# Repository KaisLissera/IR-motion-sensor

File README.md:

# IR-motion-sensor
*University graduation work*  

Система электронного хронометража для конных соревнований, временные засечки определяются по моменту пересечения луча

## TODO:
### HW
- Заменить SX1276 на аналогичный модуль без интегрированной антенны или RFM95W
- Добавить на плате земляной полигон без маски для тестирования
- ZQ3 - дорожки от кварца должны быть на верхней части платы
- Заменить все резисторы и конденсаторы 0402 на 0603
- Заменить индуктивности в фильтре аналогового питания на дроссели BLM18AG102 0603
### 3d Model
- Переделать отверстие под USB порт
- ~~Подобрать размер кнопки на передней панели~~
- Облегчить корпус

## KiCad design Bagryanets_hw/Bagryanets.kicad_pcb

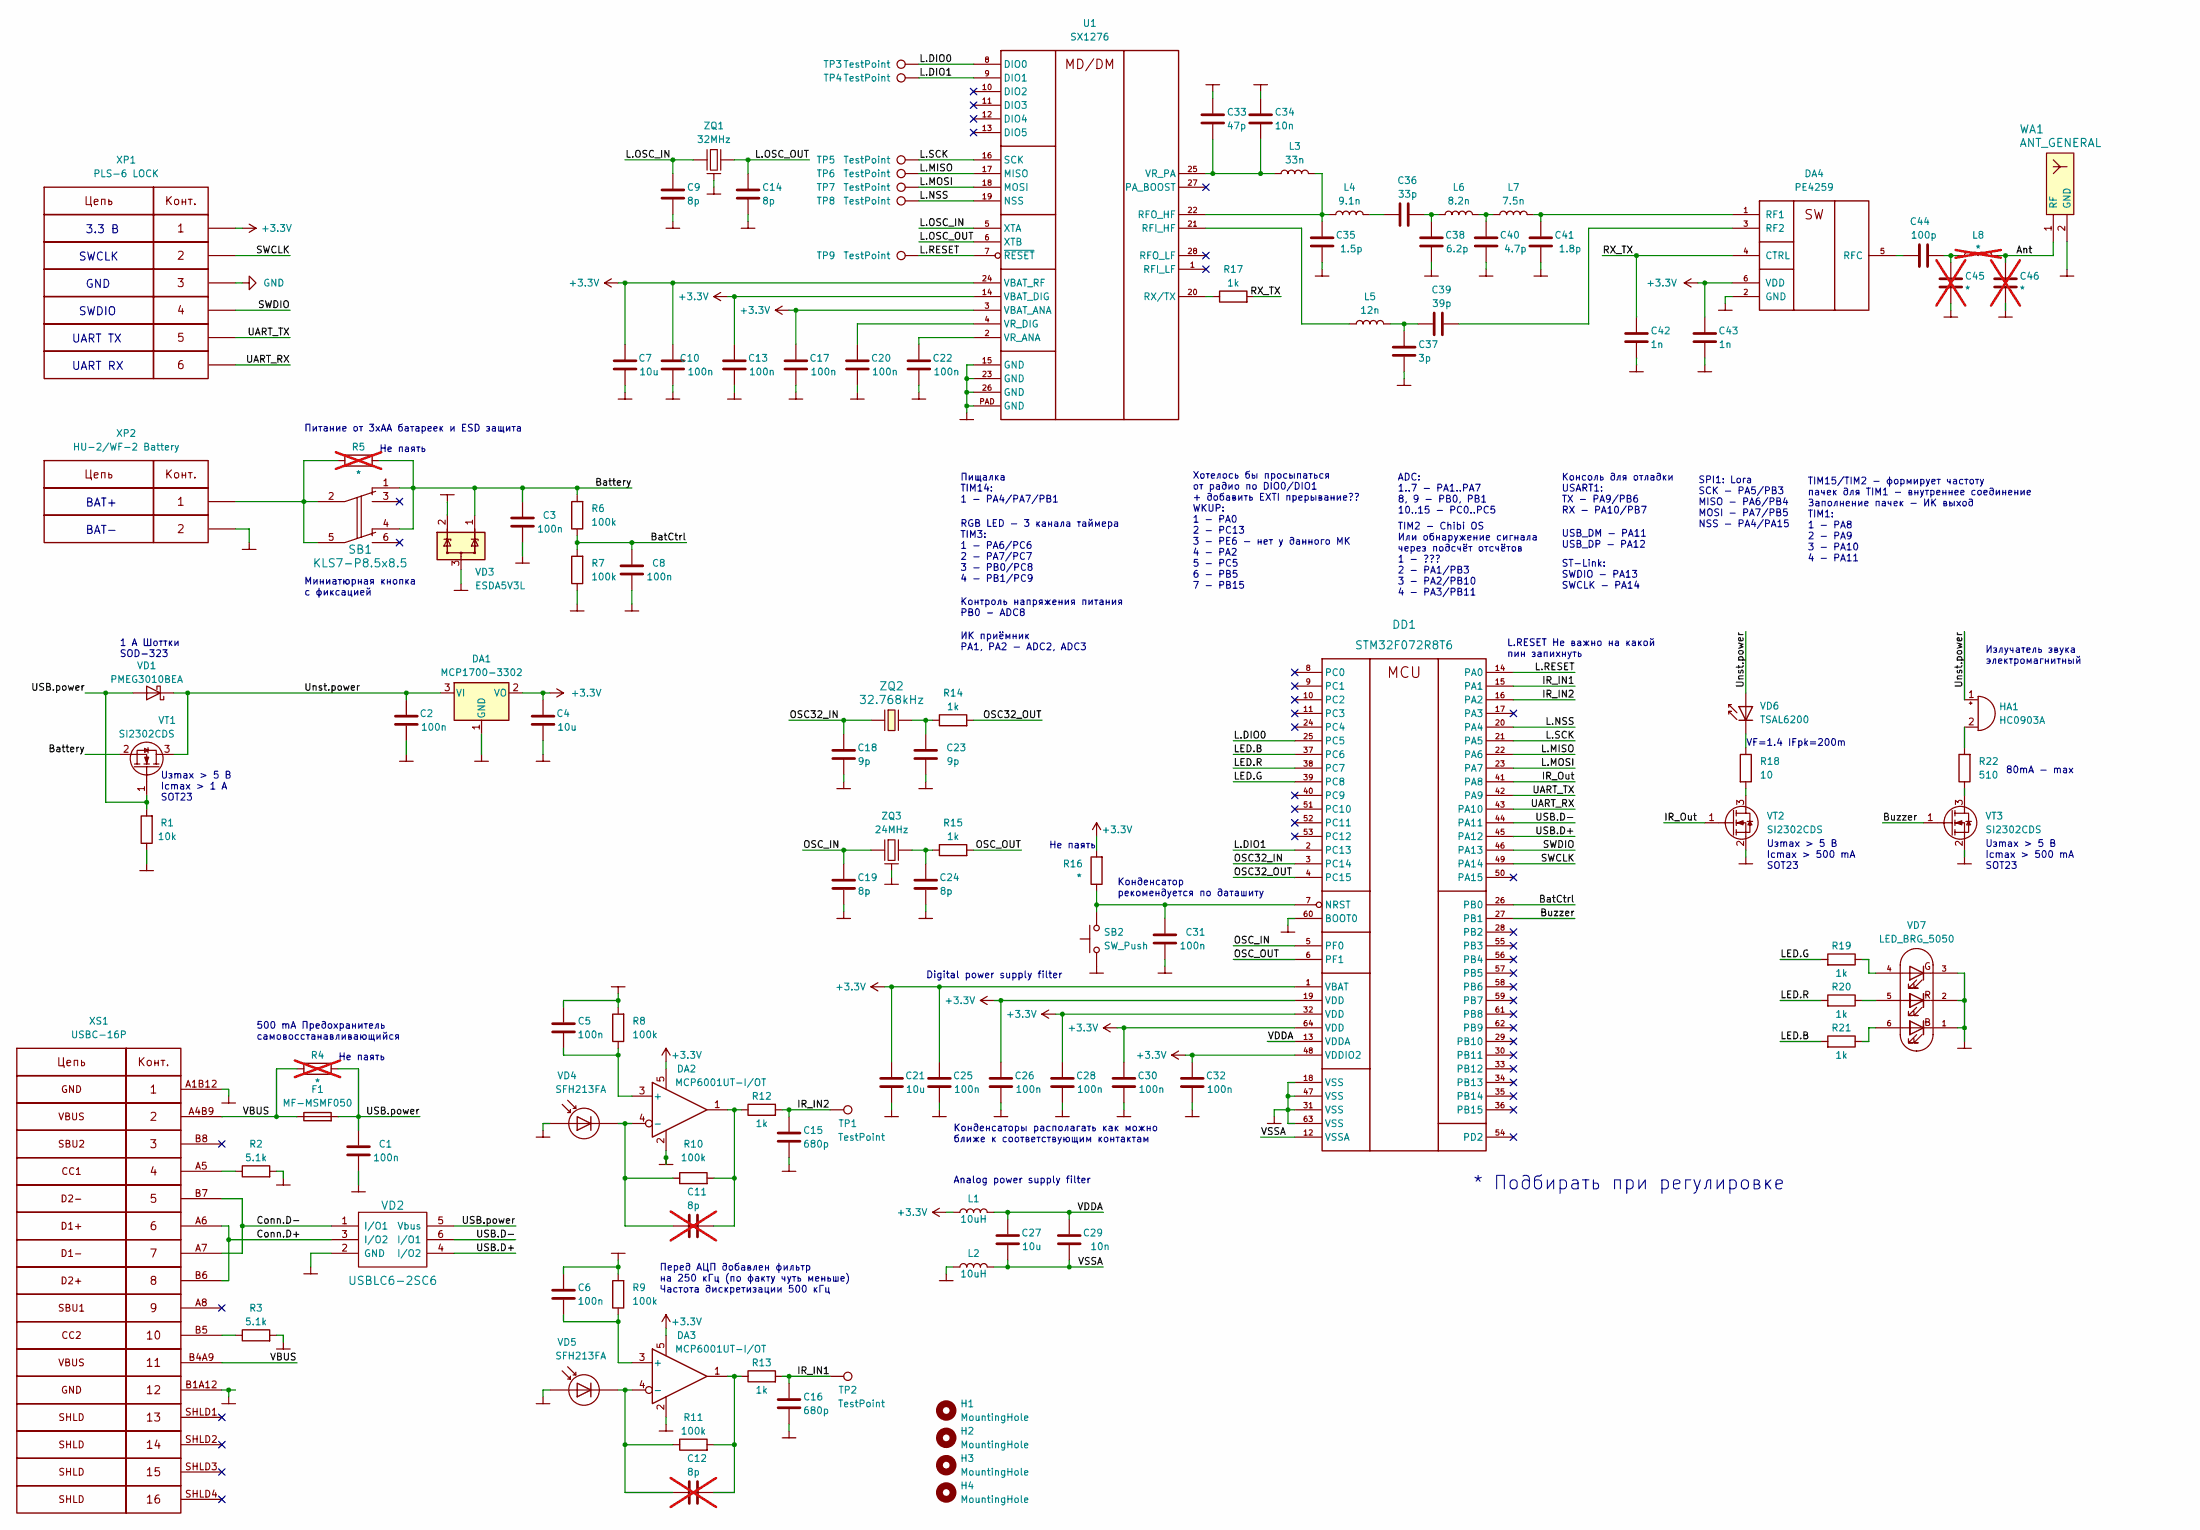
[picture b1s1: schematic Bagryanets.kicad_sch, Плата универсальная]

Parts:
C1, C2, C3, C5, C6, C8, C10, C13, C17, C20, C22, C25, C26, C28, C30, C31, C32: 100n; CAP_0402
C4, C7, C21, C27: 10u; CAP_0603
C9, C14, C19, C24: 8p; CAP_0402
C11, C12: 8p; CAP_0402; not fitted
C15, C16: 680p; CAP_0402
C18, C23: 9p; CAP_0402
C29, C34: 10n; CAP_0402
C33: 47p; CAP_0402
C35: 1.5p; CAP_0402
C36: 33p; CAP_0402
C37: 3p; CAP_0402
C38: 6.2p; CAP_0402
C39: 39p; CAP_0402
C40: 4.7p; CAP_0402
C41: 1.8p; CAP_0402
C42, C43: 1n; CAP_0402
C44: 100p; CAP_0402
C45, C46: *; CAP_0402; not fitted
DA1: MCP1700-3302; SOT23-3
DA2, DA3: MCP6001UT-I/OT; SOT23-5
DA4: PE4259; SC70
DD1: STM32F072R8T6; LQFP64
F1: MF-MSMF050; Fuse_1812_4532Metric_Pad1.30x3.40mm_HandSolder
H1, H2, H3, H4: MountingHole; MountingHole_2.5mm
HA1: HC0903A; MagneticBuzzer_CUI_CST-931RP-A
L1, L2: 10uH; IND_0805
L3: 33n; IND_0402
L4: 9.1n; IND_0402
L5: 12n; IND_0402
L6: 8.2n; IND_0402
L7: 7.5n; IND_0402
L8: *; IND_0402; not fitted
R1: 10k; RES_0603
R2, R3: 5.1k; RES_0603
R4, R5: *; RES_0402; not fitted
R6, R7, R8, R9, R10, R11: 100k; RES_0603
R12, R13, R14, R15, R19, R20, R21: 1k; RES_0603
R16: *; RES_0603
R17: 1k; RES_0402
R18: 10; RES_0402
R22: 510; RES_0402
SB1: KLS7-P8.5x8.5
SB2: SW_Push; SW_PUSH_6mm
TP1, TP2, TP3, TP4, TP5, TP6, TP7, TP8, TP9: TestPoint; TESTPOINT_1MM
U1: SX1276; QFN-28_EP_6x6_Pitch0.65mm
VD1: PMEG3010BEA; SOD323
VD2: USBLC6-2SC6; SOT23-6
VD3: ESDA5V3L; SOT-23
VD4, VD5: SFH213FA; LED_D5.0mm
VD6: TSAL6200; LED_D5.0mm_Clear
VD7: LED_BRG_5050; LED_RGB_5050-6
VT1, VT2, VT3: SI2302CDS; SOT23-3
WA1: ANT_GENERAL; Antenna_868_Bagryanets
XP1: PLS-6 LOCK; PinHeader_1x06_P2.54mm_Horizontal
XP2: HU-2/WF-2 Battery; PinHeader_1x02_P2.54mm_Horizontal
XS1: USBC-16P; USBC_10PF-074
ZQ1: 32MHz; 03225C4
ZQ2: 32.768kHz; Crystal_SMD_3215-2Pin_3.2x1.5mm
ZQ3: 24MHz; 03225C4

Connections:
+3V3: C4.2, C7.2, C10.2, C13.2, C17.2, C21.2, C25.2, C26.2, C28.2, C30.2, C32.2, C43.1, DA1.2 (VO), DA2.5, DA3.5, DA4.6 (VDD), DD1.1 (VBAT), DD1.19 (VDD), DD1.32 (VDD), DD1.48 (VDDIO2), DD1.64 (VDD), L1.1, R16.2, U1.3 (VBAT_ANA), U1.14 (VBAT_DIG), U1.24 (VBAT_RF), XP1.1
/Ant: C46.1, L8.2, WA1.1 (RF)
/BatCtrl: C8.2, DD1.26 (PB0), R6.1, R7.2
/Battery: C3.2, R5.2, R6.2, SB1.1, SB1.4, VD3.1 (IO1), VT1.2 (S)
/Buzzer: DD1.27 (PB1), VT3.1 (G)
/Conn.D+: VD2.3 (I/O2), XS1.A6 (DP1), XS1.B6 (DP2)
/Conn.D-: VD2.1 (I/O1), XS1.A7 (DN1), XS1.B7 (DN2)
/IR_IN1: C16.1, DD1.15 (PA1), R13.2, TP2.1
/IR_IN2: C15.1, DD1.16 (PA2), R12.2, TP1.1
/IR_Out: DD1.41 (PA8), VT2.1 (G)
/L.DIO0: DD1.25 (PC5), TP3.1, U1.8 (DIO0)
/L.DIO1: DD1.2 (PC13), TP4.1, U1.9 (DIO1)
/L.MISO: DD1.22 (PA6), TP6.1, U1.17 (MISO)
/L.MOSI: DD1.23 (PA7), TP7.1, U1.18 (MOSI)
/L.NSS: DD1.20 (PA4), TP8.1, U1.19 (NSS)
/L.OSC_IN: C9.1, U1.5 (XTA), ZQ1.1
/L.OSC_OUT: C14.1, U1.6 (XTB), ZQ1.2
/L.RESET: DD1.14 (PA0), TP9.1, U1.7 (~RESET)
/L.SCK: DD1.21 (PA5), TP5.1, U1.16 (SCK)
/LED.B: DD1.37 (PC6), R21.2
/LED.G: DD1.39 (PC8), R19.2
/LED.R: DD1.38 (PC7), R20.2
/OSC32_IN: C18.2, DD1.3 (PC14), ZQ2.1
/OSC32_OUT: DD1.4 (PC15), R14.2
/OSC_IN: C19.2, DD1.5 (PF0), ZQ3.1
/OSC_OUT: DD1.6 (PF1), R15.2
/RX_TX: C42.1, DA4.4 (CTRL), R17.2
/SWCLK: DD1.49 (PA14), XP1.2
/SWDIO: DD1.46 (PA13), XP1.4
/UART_RX: DD1.43 (PA10), XP1.6
/UART_TX: DD1.42 (PA9), XP1.5
/USB.D+: DD1.45 (PA12), VD2.4 (I/O2)
/USB.D-: DD1.44 (PA11), VD2.6 (I/O1)
/USB.power: C1.2, F1.2, R1.2, R4.2, VD1.A, VD2.5 (Vbus), VT1.1 (G)
/Unst.power: C2.2, DA1.3 (VI), HA1.1 (-), VD1.C, VD6.2 (A), VT1.3 (D)
/VBUS: F1.1, R4.1, XS1.A4B9 (VBUS), XS1.B4A9 (VBUS)
/VDDA: C27.2, C29.2, DD1.13 (VDDA), L1.2
/VSSA: C27.1, C29.1, DD1.12 (VSSA), L2.2
unnamed: C11.1, DA2.1, R10.2, R12.1
unnamed: C12.1, DA3.1, R11.2, R13.1
unnamed: C23.2, R14.1, ZQ2.2
unnamed: C24.2, R15.1, ZQ3.2
unnamed: C36.1, L4.2
unnamed: C36.2, C38.2, L6.1
unnamed: C37.1, C39.1, L5.2
unnamed: C40.2, L6.2, L7.1
unnamed: C44.2, C45.1, L8.1
unnamed: C5.2, DA2.3 (+), R8.1
unnamed: C11.2, DA2.4 (-), R10.1, VD4.1 (K)
unnamed: C6.2, DA3.3 (+), R9.1
unnamed: C12.2, DA3.4 (-), R11.1, VD5.1 (K)
unnamed: C41.2, DA4.1 (RF1), L7.2
unnamed: C39.2, DA4.3 (RF2)
unnamed: C44.1, DA4.5 (RFC)
unnamed: C31.2, DD1.7 (NRST), R16.1, SB2.2
unnamed: HA1.2 (+), R22.2
unnamed: R5.1, SB1.2, SB1.5, XP2.1
unnamed: L5.1, U1.21 (RFI_HF)
unnamed: C35.2, L3.2, L4.1, U1.22 (RFO_HF)
unnamed: R17.1, U1.20 (RX/TX)
unnamed: C22.2, U1.2 (VR_ANA)
unnamed: C20.2, U1.4 (VR_DIG)
unnamed: C33.2, C34.2, L3.1, U1.25 (VR_PA)
unnamed: R18.1, VD6.1 (K)
unnamed: R19.1, VD7.4 (BA)
unnamed: R20.1, VD7.5 (GA)
unnamed: R21.1, VD7.6 (RA)
unnamed: R18.2, VT2.3 (D)
unnamed: R22.1, VT3.3 (D)
unnamed: R2.1, XS1.A5 (CC1)
unnamed: R3.1, XS1.B5 (CC2)

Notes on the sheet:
GND
80mA - max
Перед АЦП добавлен фильтр на 250 кГц (по факту чуть меньше) Частота дискретизации 500 кГц
Uзmax > 5 В Iсmax > 500 mА SOT23
SWDIO
Контроль напряжения питания PB0 - ADC8
500 mA Предохранитель самовосстанавливающийся
TIM15/TIM2 - формирует частоту пачек для TIM1 - внутреннее соединение Заполнение пачек - ИК выход TIM1: 1 - PA8 2 - PA9 3 - PA10 4 - PA11
Не паять
Uзmax > 5 В Iсmax > 1 А SOT23
L.RESET Не важно на какой пин запихнуть
ИК приёмник PA1, PA2 - ADC2, ADC3
Излучатель звука электромагнитный
TIM2 - Chibi OS Или обнаружение сигнала через подсчёт отсчётов 1 - ??? 2 - PA1/PB3 3 - PA2/PB10 4 - PA3/PB11
BAT-
Analog power supply filter
RGB LED - 3 канала таймера TIM3: 1 - PA6/PC6 2 - PA7/PC7 3 - PB0/PC8 4 - PB1/PC9
3.3 В
UART TX
USB_DM - PA11 USB_DP - PA12
* Подбирать при регулировке
BAT+
Миниатюрная кнопка с фиксацией
Консоль для отладки USART1: TX - PA9/PB6 RX - PA10/PB7
Хотелось бы просыпаться от радио по DIO0/DIO1 + добавить EXTI прерывание?? WKUP: 1 - PA0 2 - PC13 3 - PE6 - нет у данного МК 4 - PA2 5 - PC5 6 - PB5 7 - PB15
Пищалка TIM14: 1 - PA4/PA7/PB1
Digital power supply filter
Питание от 3хАА батареек и ESD защита
Конденсатор рекомендуется по даташиту
VF=1.4 IFpk=200m
ADC: 1..7 - PA1..PA7 8, 9 - PB0, PB1 10..15 - PC0..PC5
ST-Link: SWDIO - PA13 SWCLK - PA14
1 А Шоттки SOD-323
SWCLK
UART RX
Конденсаторы располагать как можно ближе к соответствующим контактам
SPI1: Lora SCK - PA5/PB3 MISO - PA6/PB4 MOSI - PA7/PB5 NSS - PA4/PA15

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
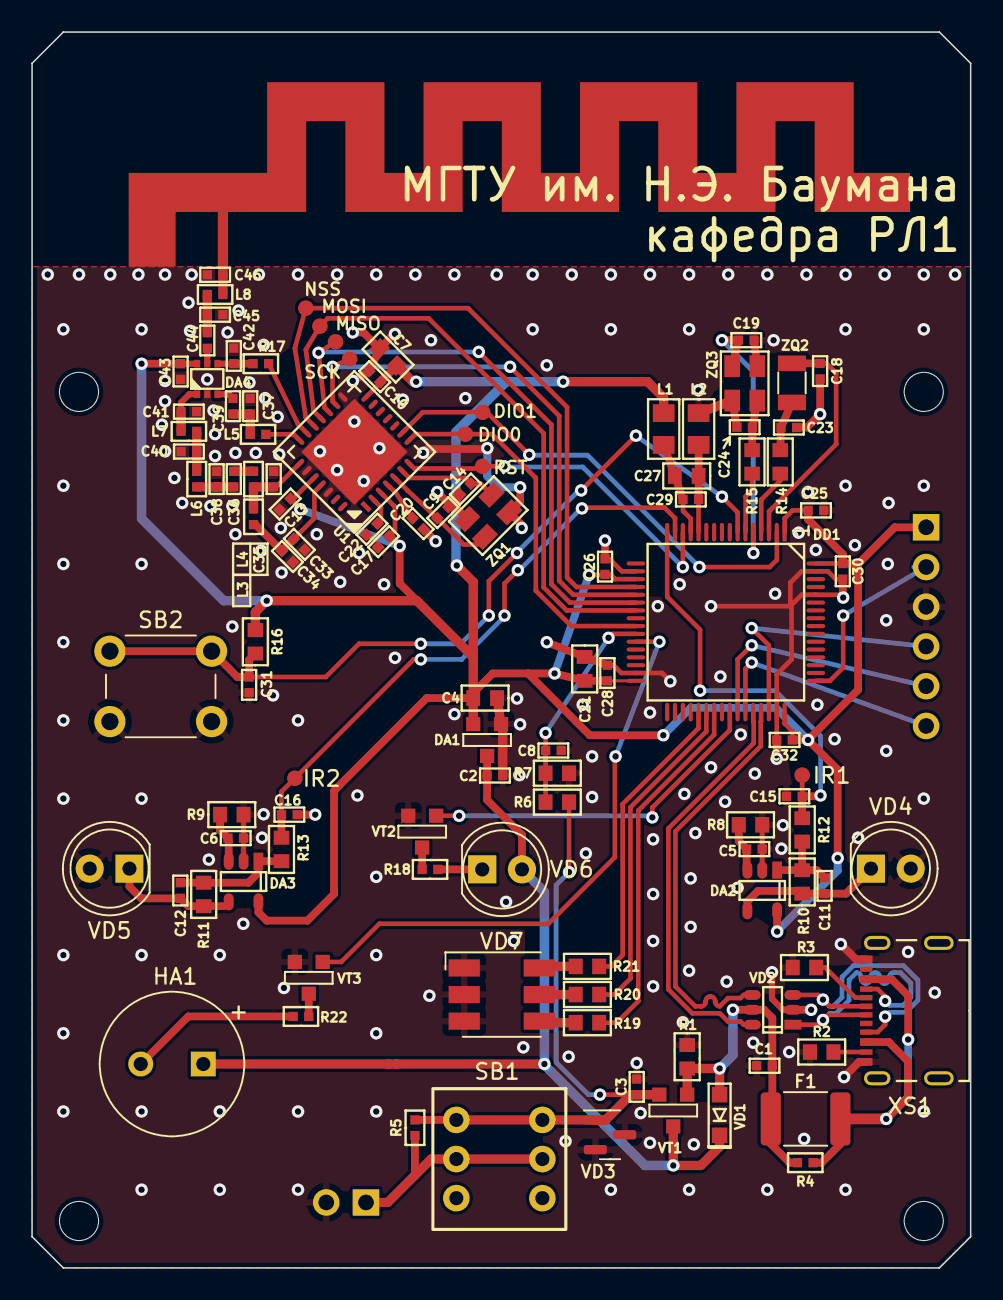
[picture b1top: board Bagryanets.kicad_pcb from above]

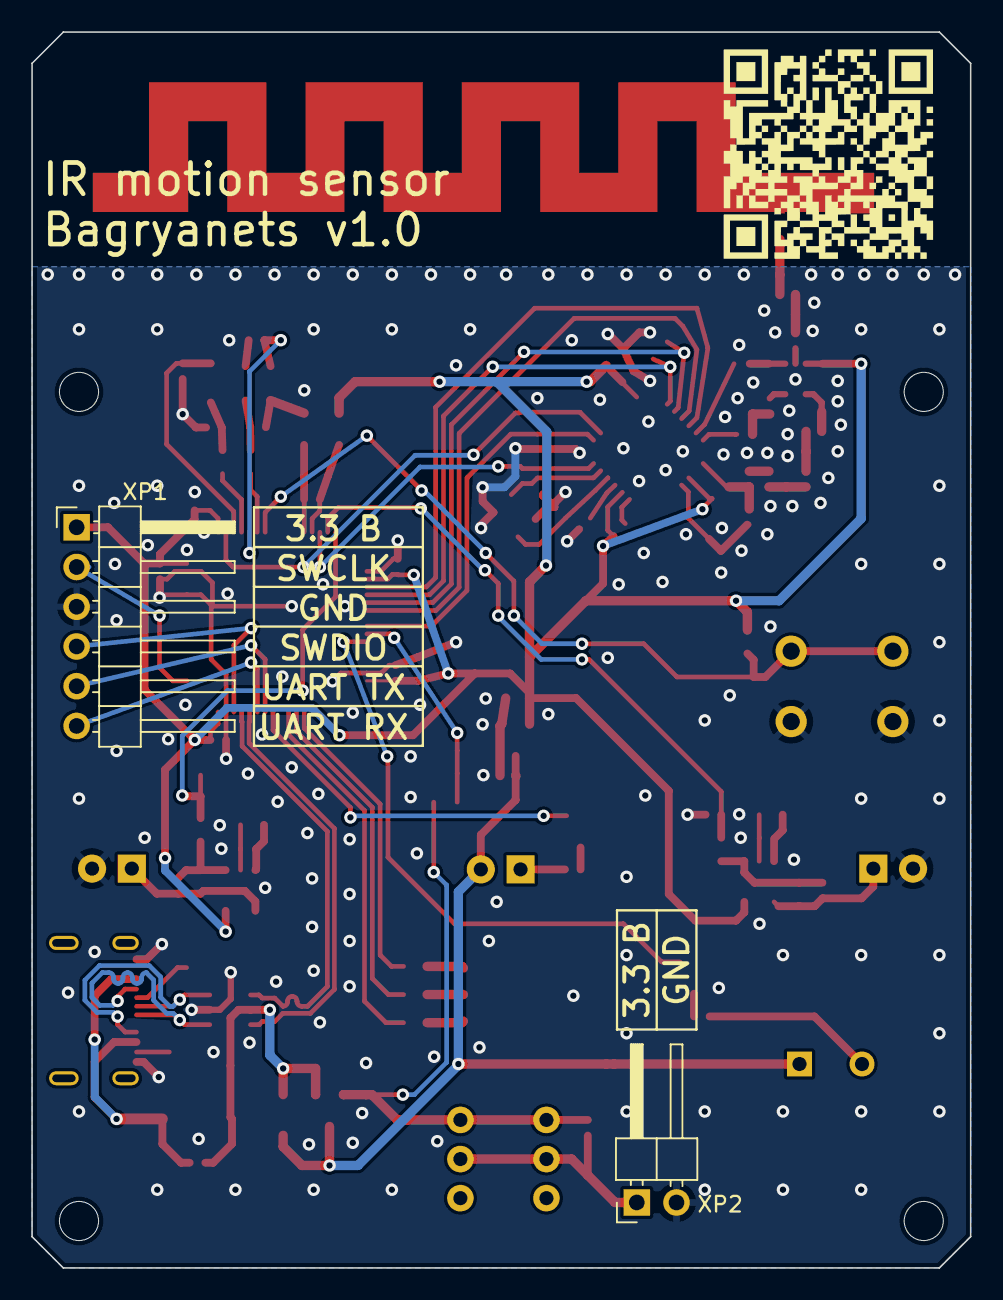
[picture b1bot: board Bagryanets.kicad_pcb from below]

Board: 2 copper layers, 60.0 x 79.0 mm, 116 parts (2 on the bottom side), 72 nets.

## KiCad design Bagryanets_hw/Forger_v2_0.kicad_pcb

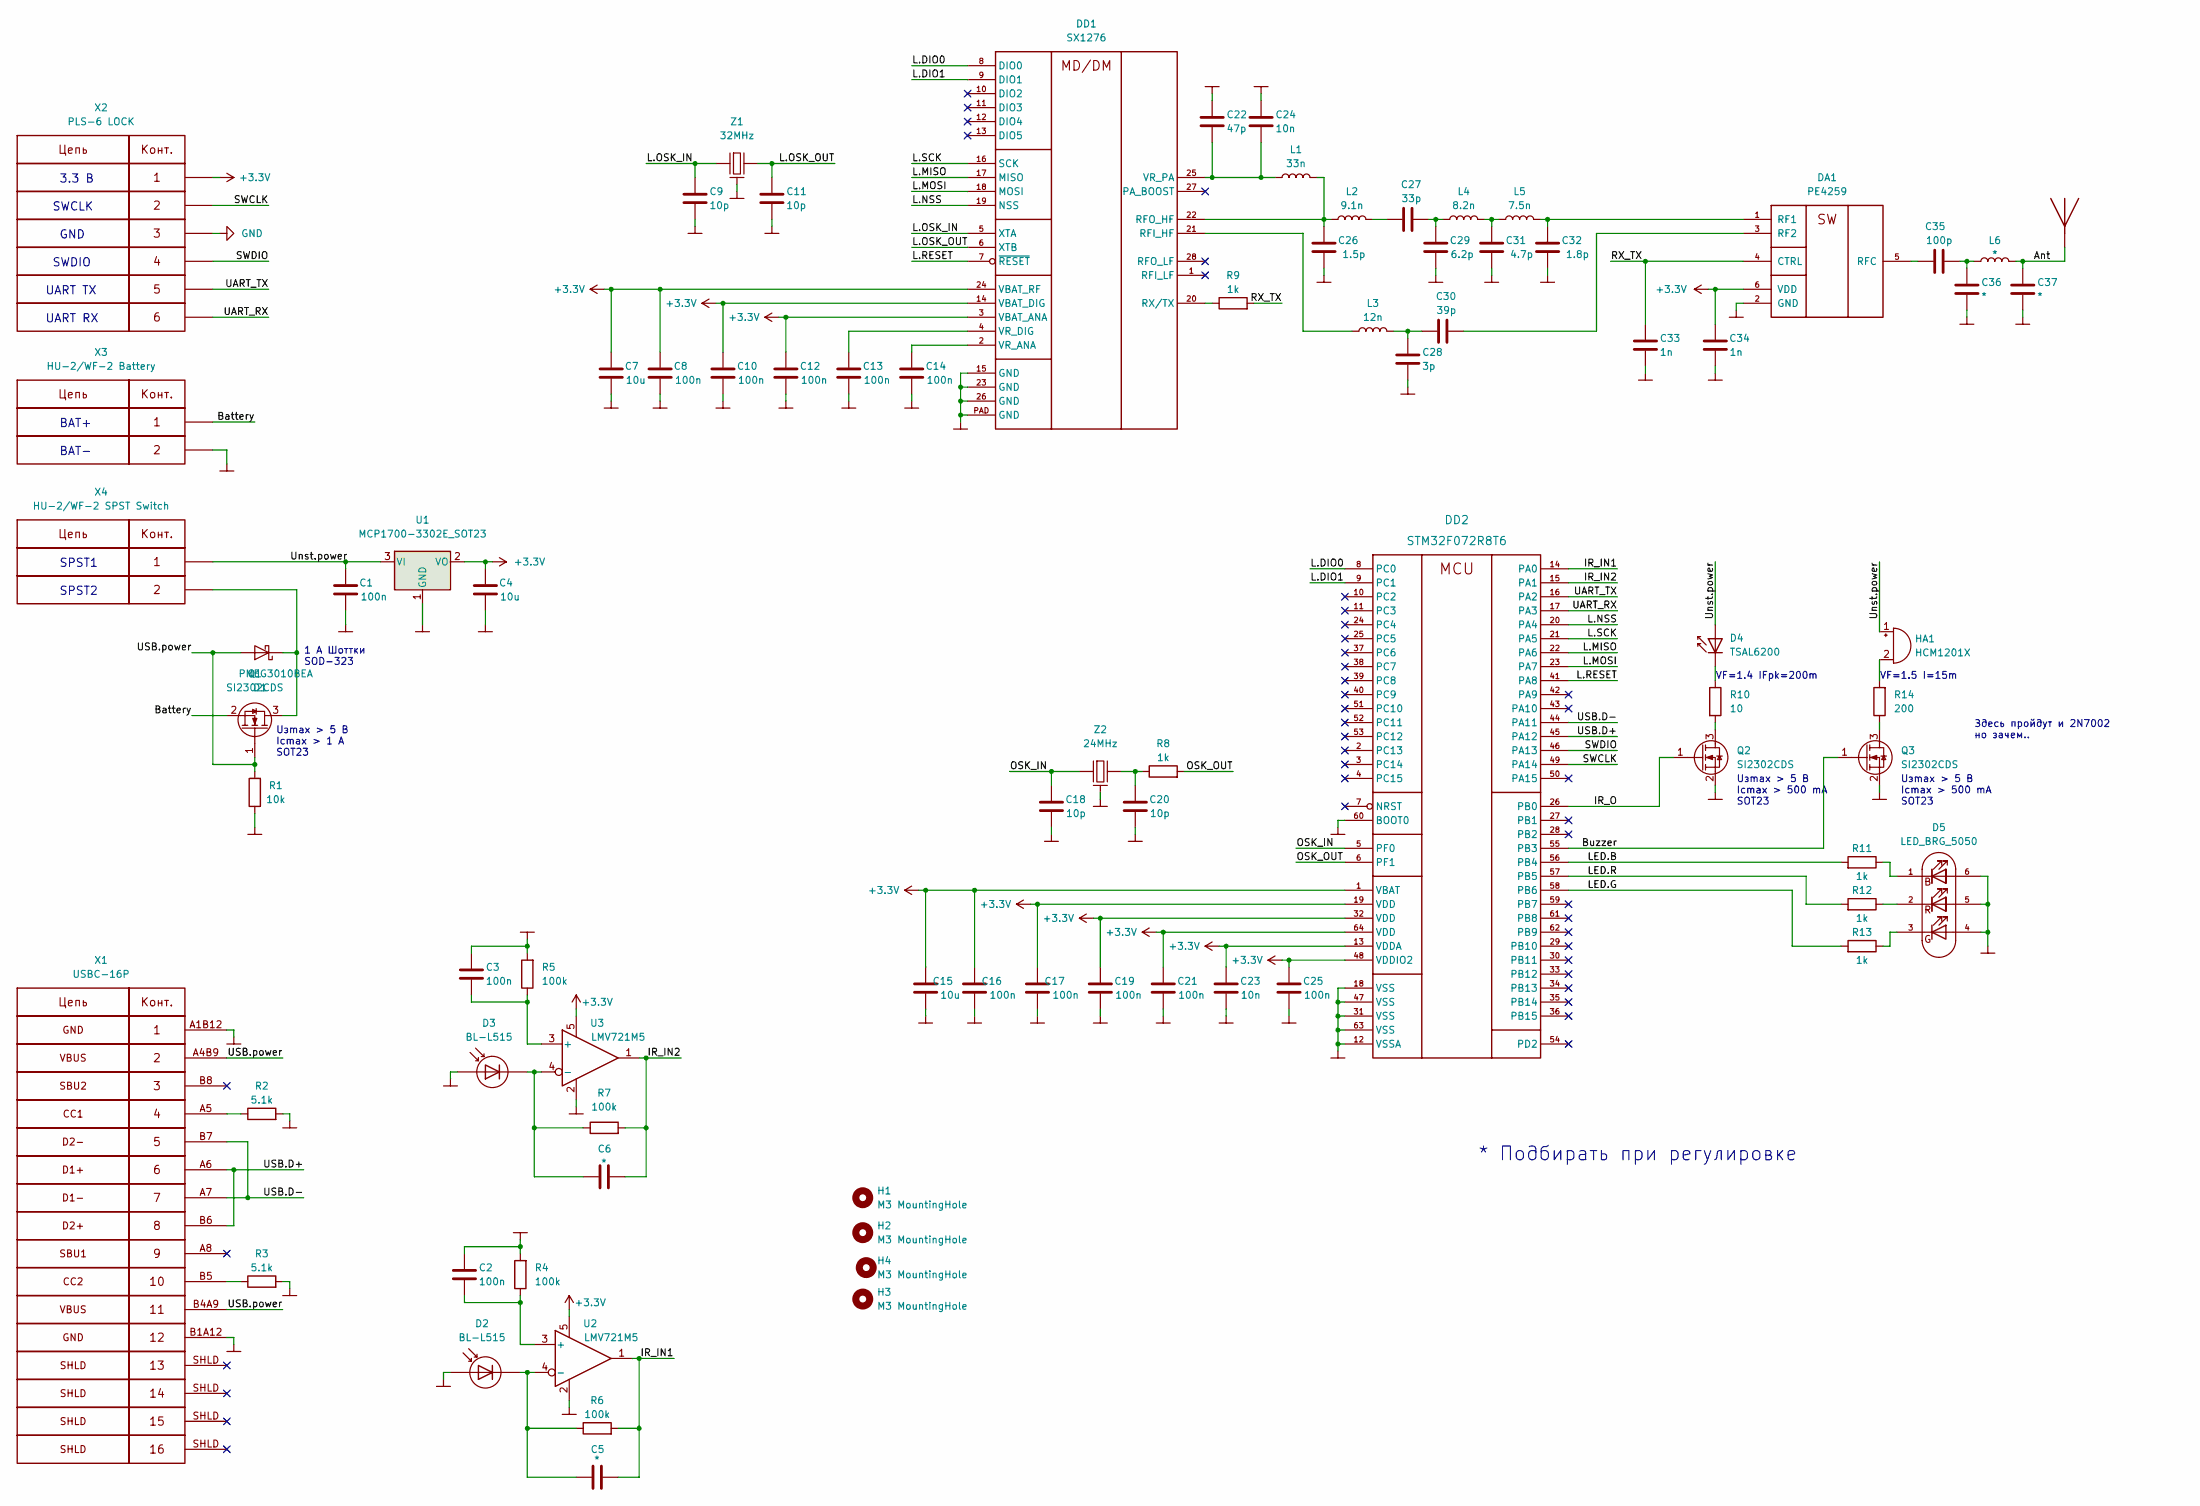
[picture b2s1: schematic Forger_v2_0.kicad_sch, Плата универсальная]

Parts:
AE1: Antenna
C1, C2, C3, C8, C10, C12, C13, C14, C16, C17, C19, C21, C25: 100n; CAP_0402
C4, C7, C15: 10u; CAP_0603
C5, C6, C36, C37: *; CAP_0402
C9, C11, C18, C20: 10p; CAP_0402
C22: 47p; CAP_0402
C23, C24: 10n; CAP_0402
C26: 1.5p; CAP_0402
C27: 33p; CAP_0402
C28: 3p; CAP_0402
C29: 6.2p; CAP_0402
C30: 39p; CAP_0402
C31: 4.7p; CAP_0402
C32: 1.8p; CAP_0402
C33, C34: 1n; CAP_0402
C35: 100p; CAP_0402
D1: PMEG3010BEA; SOD323
D2, D3: BL-L515; LED_D5.0mm
D4: TSAL6200; LED_D5.0mm_Clear
D5: LED_BRG_5050; LED_RGB_5050-6
DA1: PE4259; SC70
DD1: SX1276; QFN-28_EP_6x6_Pitch0.65mm
DD2: STM32F072R8T6; LQFP64
H1, H2, H3, H4: M3 MountingHole; MountingHole_3.2mm_M3
HA1: HCM1201X; Buzzer_12x9.5RM7.6
L1: 33n; IND_0402
L2: 9.1n; IND_0402
L3: 12n; IND_0402
L4: 8.2n; IND_0402
L5: 7.5n; IND_0402
L6: *; IND_0402
Q1, Q2, Q3: SI2302CDS; SOT23-3
R1: 10k; RES_0603
R2, R3: 5.1k; RES_0603
R4, R5, R6, R7: 100k; RES_0603
R8, R9, R11, R12, R13: 1k; RES_0402
R10: 10; RES_0402
R14: 200; RES_0402
U1: MCP1700-3302E_SOT23; SOT23-3
U2, U3: LMV721M5; SOT23-5
X1: USBC-16P; USBC_10PF-074
X2: PLS-6 LOCK; PLS-6_LOCK
X3: HU-2/WF-2 Battery; PinHeader_1x02_P2.54mm_Vertical
X4: HU-2/WF-2 SPST Switch; PinHeader_1x02_P2.54mm_Vertical
Z1: 32MHz; 03225C4
Z2: 24MHz; 03225C4

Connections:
+3V3: C4.2, C7.2, C8.2, C10.2, C12.2, C15.2, C16.2, C17.2, C19.2, C21.2, C23.2, C25.2, C34.1, DA1.6 (VDD), DD1.3 (VBAT_ANA), DD1.14 (VBAT_DIG), DD1.24 (VBAT_RF), DD2.1 (VBAT), DD2.13 (VDDA), DD2.19 (VDD), DD2.32 (VDD), DD2.48 (VDDIO2), DD2.64 (VDD), U1.2 (VO), U2.5, U3.5, X2.1
/Ant: AE1.1, C37.1, L6.2
/Battery: Q1.2 (S), X3.1
/Buzzer: DD2.55 (PB3), Q3.1 (G)
/IR_IN1: C5.1, DD2.14 (PA0), R6.2, U2.1
/IR_IN2: C6.1, DD2.15 (PA1), R7.2, U3.1
/IR_O: DD2.26 (PB0), Q2.1 (G)
/L.DIO0: DD1.8 (DIO0), DD2.8 (PC0)
/L.DIO1: DD1.9 (DIO1), DD2.9 (PC1)
/L.MISO: DD1.17 (MISO), DD2.22 (PA6)
/L.MOSI: DD1.18 (MOSI), DD2.23 (PA7)
/L.NSS: DD1.19 (NSS), DD2.20 (PA4)
/L.OSK_IN: C9.1, DD1.5 (XTA), Z1.1
/L.OSK_OUT: C11.1, DD1.6 (XTB), Z1.2
/L.RESET: DD1.7 (~RESET), DD2.41 (PA8)
/L.SCK: DD1.16 (SCK), DD2.21 (PA5)
/LED.B: DD2.56 (PB4), R11.2
/LED.G: DD2.58 (PB6), R13.2
/LED.R: DD2.57 (PB5), R12.2
/OSK_IN: C18.2, DD2.5 (PF0), Z2.1
/OSK_OUT: DD2.6 (PF1), R8.2
/RX_TX: C33.1, DA1.4 (CTRL), R9.2
/SWCLK: DD2.49 (PA14), X2.2
/SWDIO: DD2.46 (PA13), X2.4
/UART_RX: DD2.17 (PA3), X2.6
/UART_TX: DD2.16 (PA2), X2.5
/USB.D+: DD2.45 (PA12), X1.A6 (DP1), X1.B6 (DP2)
/USB.D-: DD2.44 (PA11), X1.A7 (DN1), X1.B7 (DN2)
/USB.power: D1.A, Q1.1 (G), R1.2, X1.A4B9 (VBUS), X1.B4A9 (VBUS)
/Unst.power: C1.2, D4.2 (A), HA1.1 (-), U1.3 (VI), X4.1
unnamed: C2.2, R4.1, U2.3 (+)
unnamed: C3.2, R5.1, U3.3 (+)
unnamed: C5.2, D2.1 (K), R6.1, U2.4 (-)
unnamed: C6.2, D3.1 (K), R7.1, U3.4 (-)
unnamed: C13.2, DD1.4 (VR_DIG)
unnamed: C14.2, DD1.2 (VR_ANA)
unnamed: C20.2, R8.1, Z2.2
unnamed: C22.2, C24.2, DD1.25 (VR_PA), L1.1
unnamed: C26.2, DD1.22 (RFO_HF), L1.2, L2.1
unnamed: C27.1, L2.2
unnamed: C27.2, C29.2, L4.1
unnamed: C28.1, C30.1, L3.2
unnamed: C30.2, DA1.3 (RF2)
unnamed: C31.2, L4.2, L5.1
unnamed: C32.2, DA1.1 (RF1), L5.2
unnamed: C35.1, DA1.5 (RFC)
unnamed: C35.2, C36.1, L6.1
unnamed: D4.1 (K), R10.1
unnamed: D5.1 (RK), R11.1
unnamed: D5.2 (GK), R12.1
unnamed: D5.3 (BK), R13.1
unnamed: DD1.20 (RX/TX), R9.1
unnamed: DD1.21 (RFI_HF), L3.1
unnamed: HA1.2 (+), R14.2
unnamed: D1.C, Q1.3 (D), X4.2
unnamed: Q2.3 (D), R10.2
unnamed: Q3.3 (D), R14.1
unnamed: R2.1, X1.A5 (CC1)
unnamed: R3.1, X1.B5 (CC2)

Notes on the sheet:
GND
VF=1.5 I=15m
SPST1
Uзmax > 5 В Iсmax > 500 mА SOT23
SWDIO
Uзmax > 5 В Iсmax > 1 А SOT23
SPST2
Здесь пройдут и 2N7002 но зачем..
BAT-
3.3 В
UART TX
* Подбирать при регулировке
BAT+
VF=1.4 IFpk=200m
1 А Шоттки SOD-323
SWCLK
UART RX

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
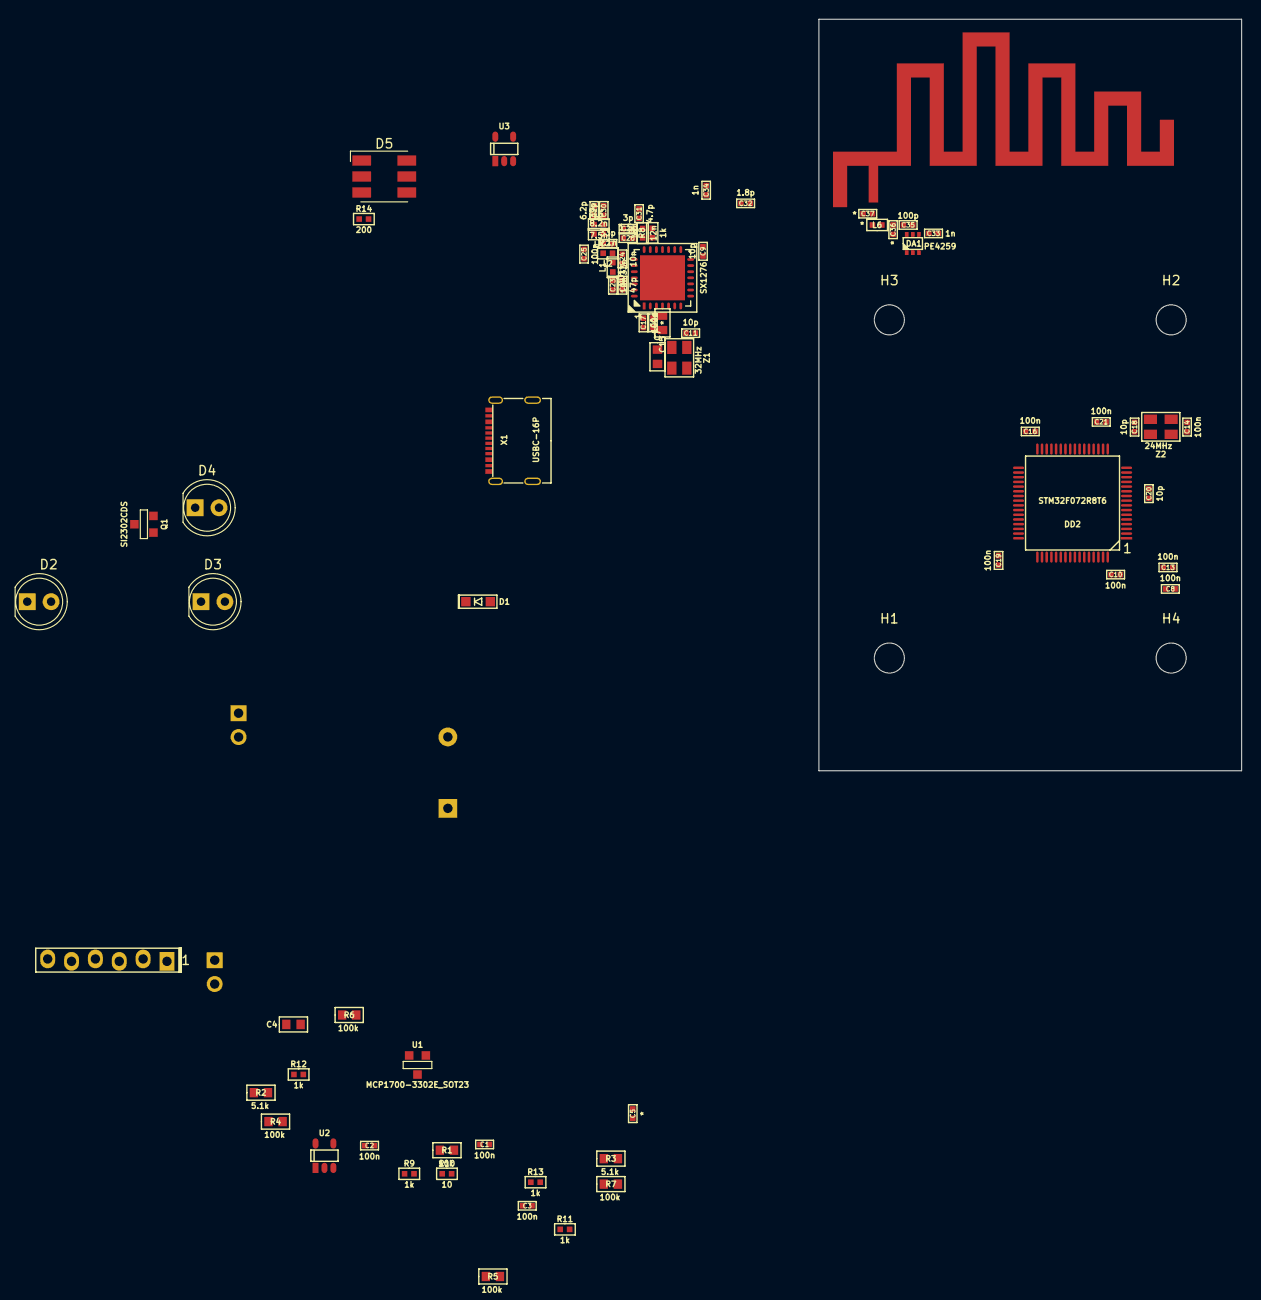
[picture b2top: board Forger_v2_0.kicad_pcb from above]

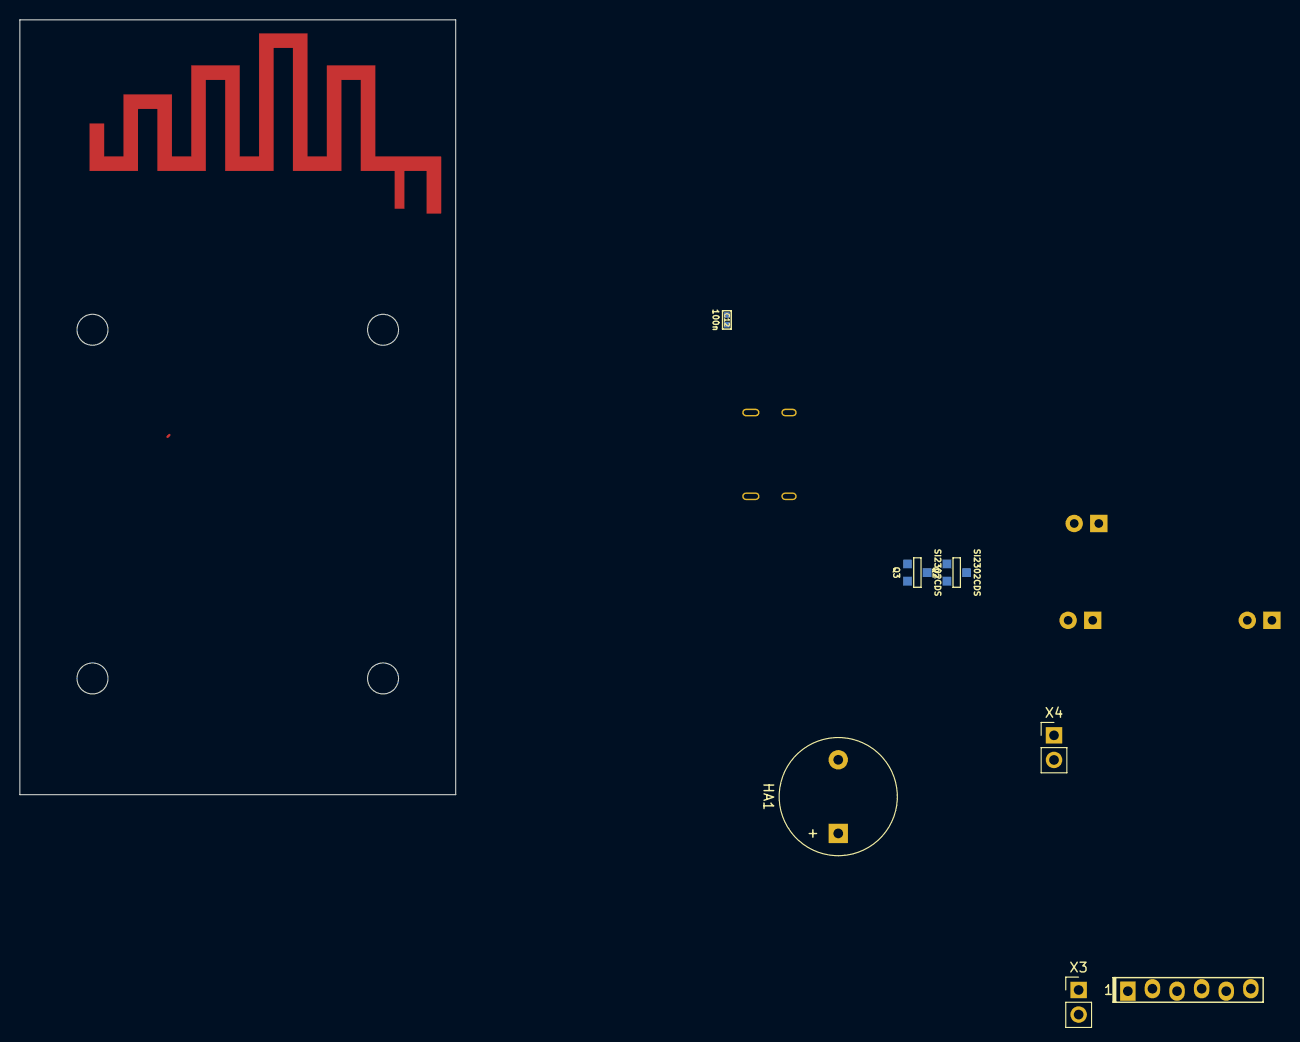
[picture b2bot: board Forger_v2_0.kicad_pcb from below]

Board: 2 copper layers, 45.0 x 80.0 mm, 82 parts (7 on the bottom side), 60 nets.

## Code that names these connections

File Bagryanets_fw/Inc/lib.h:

/*
 * ezhLib.h
 *
 *  Created on: 2023.07.31
 *      Author: Kais_Lissera
 */

#ifndef INC_LIB_H_
#define INC_LIB_H_

#include <board.h>

#include <stm32f072xb.h>

//GPIO pins definitions
/////////////////////////////////////////////////////////////////////
#define PA0		GPIOA, 0
#define PA1		GPIOA, 1
#define PA2		GPIOA, 2
#define PA3		GPIOA, 3
#define PA4		GPIOA, 4
#define PA5		GPIOA, 5
#define PA6		GPIOA, 6
#define PA7		GPIOA, 7
#define PA8		GPIOA, 8
#define PA9		GPIOA, 9
#define PA10	GPIOA, 10
#define PA11	GPIOA, 11
#define PA12	GPIOA, 12
#define PA13	GPIOA, 13
#define PA14	GPIOA, 14
#define PA15	GPIOA, 15

#define PB0		GPIOB, 0
#define PB1		GPIOB, 1
#define PB2		GPIOB, 2
#define PB3		GPIOB, 3
#define PB4		GPIOB, 4
#define PB5		GPIOB, 5
#define PB6		GPIOB, 6
#define PB7		GPIOB, 7
#define PB8		GPIOB, 8
#define PB9		GPIOB, 9
#define PB10	GPIOB, 10
#define PB11	GPIOB, 11
#define PB12	GPIOB, 12
#define PB13	GPIOB, 13
#define PB14	GPIOB, 14
#define PB15	GPIOB, 15

#define PC0		GPIOC, 0
#define PC1		GPIOC, 1
#define PC2		GPIOC, 2
#define PC3		GPIOC, 3
#define PC4		GPIOC, 4
#define PC5		GPIOC, 5
#define PC6		GPIOC, 6
#define PC7		GPIOC, 7
#define PC8		GPIOC, 8
#define PC9		GPIOC, 9
#define PC10	GPIOC, 10
#define PC11	GPIOC, 11
#define PC12	GPIOC, 12
#define PC13	GPIOC, 13
#define PC14	GPIOC, 14
#define PC15	GPIOC, 15

//Return values
/////////////////////////////////////////////////////////////////////

typedef enum {
	retvOk,
	retvFail,
	retvTimeout,
	retvBusy,
	retvInProgress,
	retvCmdError,
	retvCmdUnknown,
	retvBadValue,
	retvNew,
	retvSame,
	retvLast,
	retvEmpty,
	retvOverflow,
	retvNotANumber,
	retvWriteProtect,
	retvWriteError,
	retvEndOfFile,
	retvNotFound,
	retvBadState,
	retvDisconnected,
	retvCollision,
	retvCRCError,
	retvNACK,
	retvNoAnswer,
	retvOutOfMemory,
	retvNotAuthorised,
	retvNoChanges,
	retvTooHighSystemClock
} retv_t;

typedef enum {
	Enable 		= 0,
	Disable 	= 1
} Ability_t;

//Simple assert
/////////////////////////////////////////////////////////////////////

#define ASSERT_SIMPLE(x) if((x) == 0) { while(1); }

//Simple circular buffer template - not used for now
/////////////////////////////////////////////////////////////////////
//Example
//static CircBuffer_t<uint8_t,1024> test;

template <typename T, uint32_t Size>
class CircBuffer_t {
private:
	T Buffer_[Size];
	uint32_t start_;
	uint32_t end_;
public:
	CircBuffer_t() {
		start_ = 0;
		end_ = 0;
	}
	T Read() {
		T temp = Buffer_[start_];
		start_ = (start_ + 1) % Size;
		return temp;
	}
	uint32_t Length() {
		if (end_ > start_)
			return end_ - start_;
		else
			return Size - start_ + end_;
	}
	void Write(T data) {
		end_ = (end_ + 1) % Size;
		Buffer_[end_] = data;
	}
	void Clear() {
		start_ = 0;
		end_ = 0;
	}
};

//Commands templates
/////////////////////////////////////////////////////////////////////

/*Callback without arguments
 * Example:
 * void HelpCallback();
 * Command_t Help((char*)"help", HelpCallback);
*/
struct Command_t {
	const char* Name;
	void (*Callback)();

	Command_t(const char* _Name, void (*_Callback)()) {
		Name = _Name;
		Callback = _Callback;
	}
};

/*Callback with argument
 * Example:
 * void EchoCallback(uint32_t);
 * CommandWithArgs_t Echo((char*)"echo", EchoCallback);
 */
struct CommandWithArgs_t {
	const char* Name;
	void (*Callback)(uint32_t);

	CommandWithArgs_t(const char* _Name, void (*_Callback)(uint32_t)) {
		Name = _Name;
		Callback = _Callback;
	}
};

#endif /* INC_LIB_H_ */

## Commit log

2023-09-05 Renamed some files
2023-09-06 Updated schematic
2023-09-28 Added analog power supply filter
2023-10-14 Added casing
2023-10-31 PCB wiring, updated casing
2023-11-14 Added LSE clock, USB protection, battery monitoring to schematic, PCB rewiring, cover update
2023-11-19 Minor PCB changes
2023-11-19 GOST designators
2023-11-19 Added STL
2024-01-08 Added bom, small schematic changes
2024-01-27 CST files added to gitignore
2024-01-27 .gitignore fixed
2024-01-27 Added TODO
2024-02-06 Adapting firmware for stm32f072r8t6
2024-02-07 Updated button and USB
2024-02-07 Firmware fixing
2024-02-08 Test firmware version
2024-02-09 Added FreeRTOS files
2024-02-13 First launch fixes
2024-02-18 Add ADC control
2024-02-18 New IR amplifier test
2024-02-29 Schematic update, IR amplifier working
2024-02-29 +Add signal processing
2024-03-01 DSP update
2024-03-01 gitignore update
2024-03-02 Casing with melt insert nuts
2024-03-03 Cover fix
2024-03-05 Bootloader not working
2024-03-10 printf fix
2024-03-12 Trying to reduce code size
2024-04-09 Altium schematic
2024-04-10 schematic
2024-04-10 gitignore fix
2024-04-14 Schematic update
2024-04-21 Altium schematic ready
2024-04-23 PcbLib update
2024-04-24 begin PCB routing
2024-04-29 PCB wired
2024-05-05 Gerbers
2024-05-07 Assembly drawing
2024-05-07 PCB drawing
2024-05-11 Schematic documentation
2024-05-16 Assembly drawings
2024-05-17 Assembly drawings and specifications
2024-05-18 Added parts drawings
2024-05-27 Сделаны дополнительные части ВКР
2024-06-19 RPZ finale
